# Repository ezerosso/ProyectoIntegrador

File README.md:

# Documentación para la implementación de un monitor de material particulado móvil

_Proyecto coparticipativo con la Secretaría de Ambiente de la provincia de Córdoba y la Facultad de Ciencias Exactas, físicas y Naturales de la Universidad Nacional de Córdoba._

(Después pondremos una foto con el plot bien termiando.)

## Guía práctica para la implementación del proyecto

A continuación se explicará la estructura del presente repositorio y los pasos a seguir. 

### En la carpeta Hardware se encuentra:
* Los componentes electrónicos necesarias para el dispositivo y dónde conseguirlos
* Implementación del circuito impreso PCB
* Implementación del Gabinete

### Instalación de software necesario:

* [Visual Studio Code](https://code.visualstudio.com/download) - Editor de código fuente donde se podrá visualizar el proyecto en su totalidad.

* [Extensión PlatformIo](https://platformio.org/install/ide?install=vscode) - Entorno de desarrollo Integrado (IDE) desde donde se podrá cargar el programa a la placa de desarollo.

* [Git Bash](https://gitforwindows.org/) - Software de control de versiones, necesario para [clonar el repositorio de GitHub](https://docs.github.com/es/repositories/creating-and-managing-repositories/cloning-a-repository) en nuestra PC. 

Una vez hecho esto, desde el VSC, se debe abrir el proyecto _(Archivo -> Abrir carpeta -> Buscamos en la carpeta donde se clonó el repositorio)._

A continuación se debe conectar mediante un cable USB la placa NodeMCU a cualquier puerto USB de nuestra PC. Luego cargamos el código a la placa:

Por último insertamos la Placa en los conectores de nuestra PCB como se indica en la carpeta Hardware.

Si se desea realizar una prueba preliminar, previo al montaje final, se puede realizar conexionando el circuito en una [protoboard](http://www.circuitoselectronicos.org/2007/10/el-protoboard-tableta-de-experimentacin.html) siguiendo el esquemático mostrado el el archivo esquematico.pdf que se encuentra en la carpeta KiCad (_Hardware -> Circuito impreso -> KiCad_).

<!-- *_Referencias_*

- https://programarfacil.com/blog/arduino-blog/platformio/

 -->

 # Manual de uso

 ## Acceso externo: Carga, Encendido y Extracción de microSD

Una vez se tenga el equipo implementado, en su parte inferior se tendrá acceso al switch on-off, a la extracción de la memoria microSD y al pin de carga:

 Los datos son guardados en archivos .csv que pueden ser visualizados en planillas de cálculo como el programa libre office, acomodados por día y agrupados en la carpeta Monitor PM.

(mostrar como se guardan los datos, como extraerlos y qué hacer con ellos)
(CONSULTAR A LA VIVI QUE HACER CON LOS DATOS)

 ## Pantallas y significados

 ### Una vez encendido el dispositivo cuenta con la siguiente pantalla de inicialización

#### #Si todo está correcto, es decir, todos los módulos funcionando y la tarjeta microSD insertada se espera que se encuentren los satélites necesarios mediante la interfaz gráfica animada mostrada a continación, dicha interfaz también se mostrará si se perdiera la señal en algún momento del recorrido. 

#### Si el tiempo de la interfaz de la búsqueda de satélites sumada a la de inicialización es menor a 30 segundos (tiempo necesario para la estabilización del sensor PM), se informa por pantalla de la siguiente forma:

#### Una vez estabilizado el sensor, con los satélites encontrados, la tarjeta microSD insertada y todo andando correctamente se imprime la pantalla general mostrada a continuación donde se refrescan los datos de los sensores en tiempo real que están siendo almacenados, y por otro lado también se informa el nivel de batería disponible.

#### Si desde el encendido o durante el normal funcionamiento del dispositivo se encuentra alguna falla, se informará mediante las pantallas mostradas a continuación:

##### - Se informa cuando la tarjeta microSD está mal insertada o no se encuentra los datos:

##### - Se informa cuando no se reciben datos del sensor PM, se dejan de registrar los datos:

##### - Se informa cuando no se recién datos del módulo GPS, se dejan de registrar los datos:

##### - Se informa cuando la batería está baja, no se muestran los datos pero se siguen registrando:

_Esta información también será valiosa durante el proceso de armado y pruebas del equipo, ya que informa sobre la mal conexión o funcionamiento de algún módulo o sensor._

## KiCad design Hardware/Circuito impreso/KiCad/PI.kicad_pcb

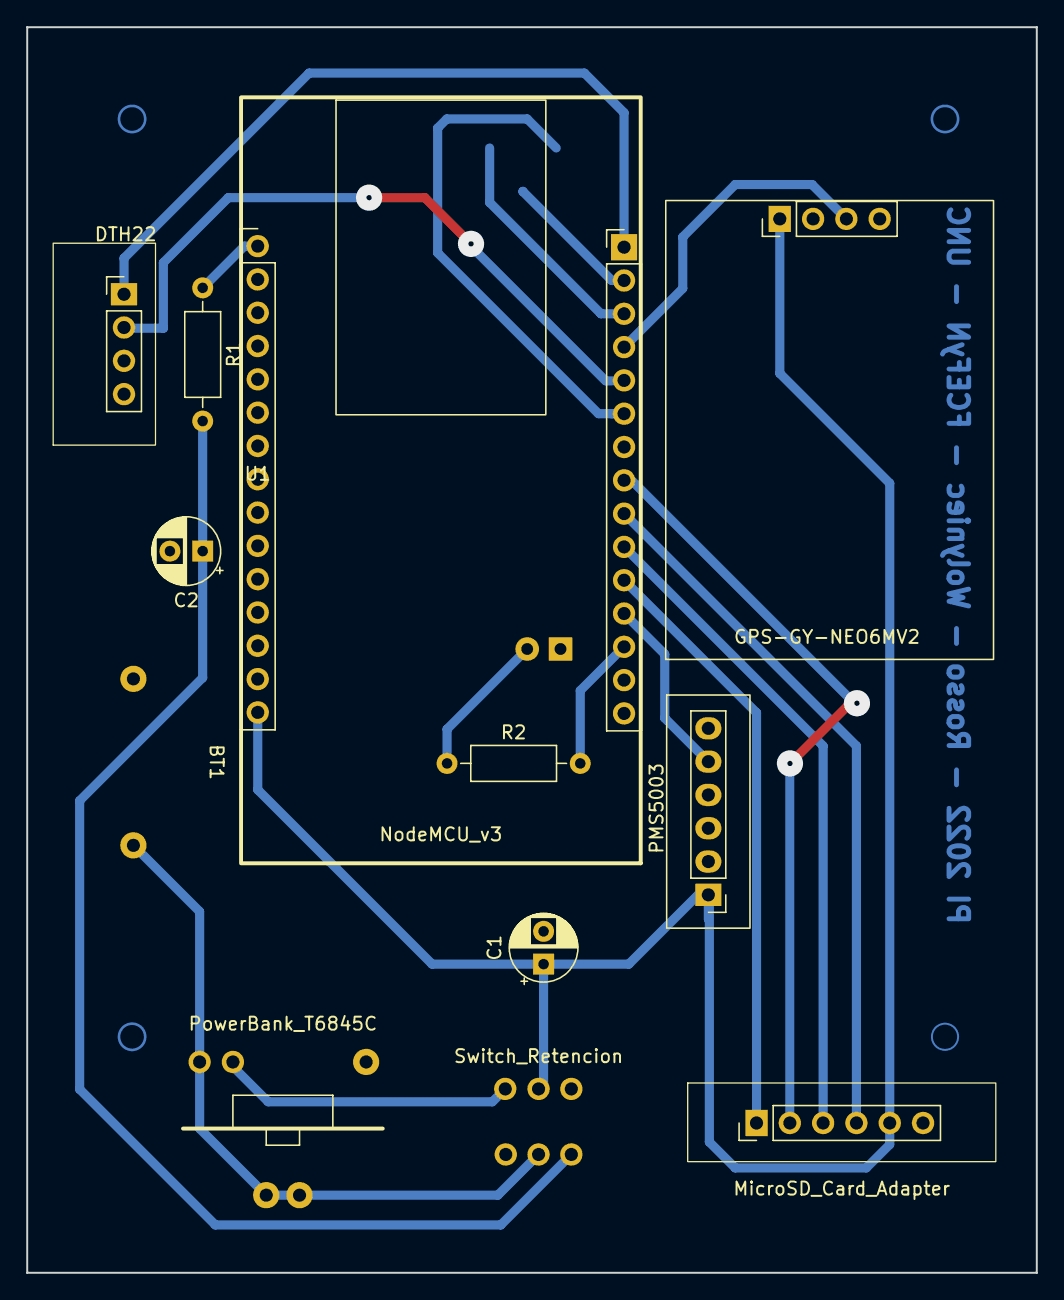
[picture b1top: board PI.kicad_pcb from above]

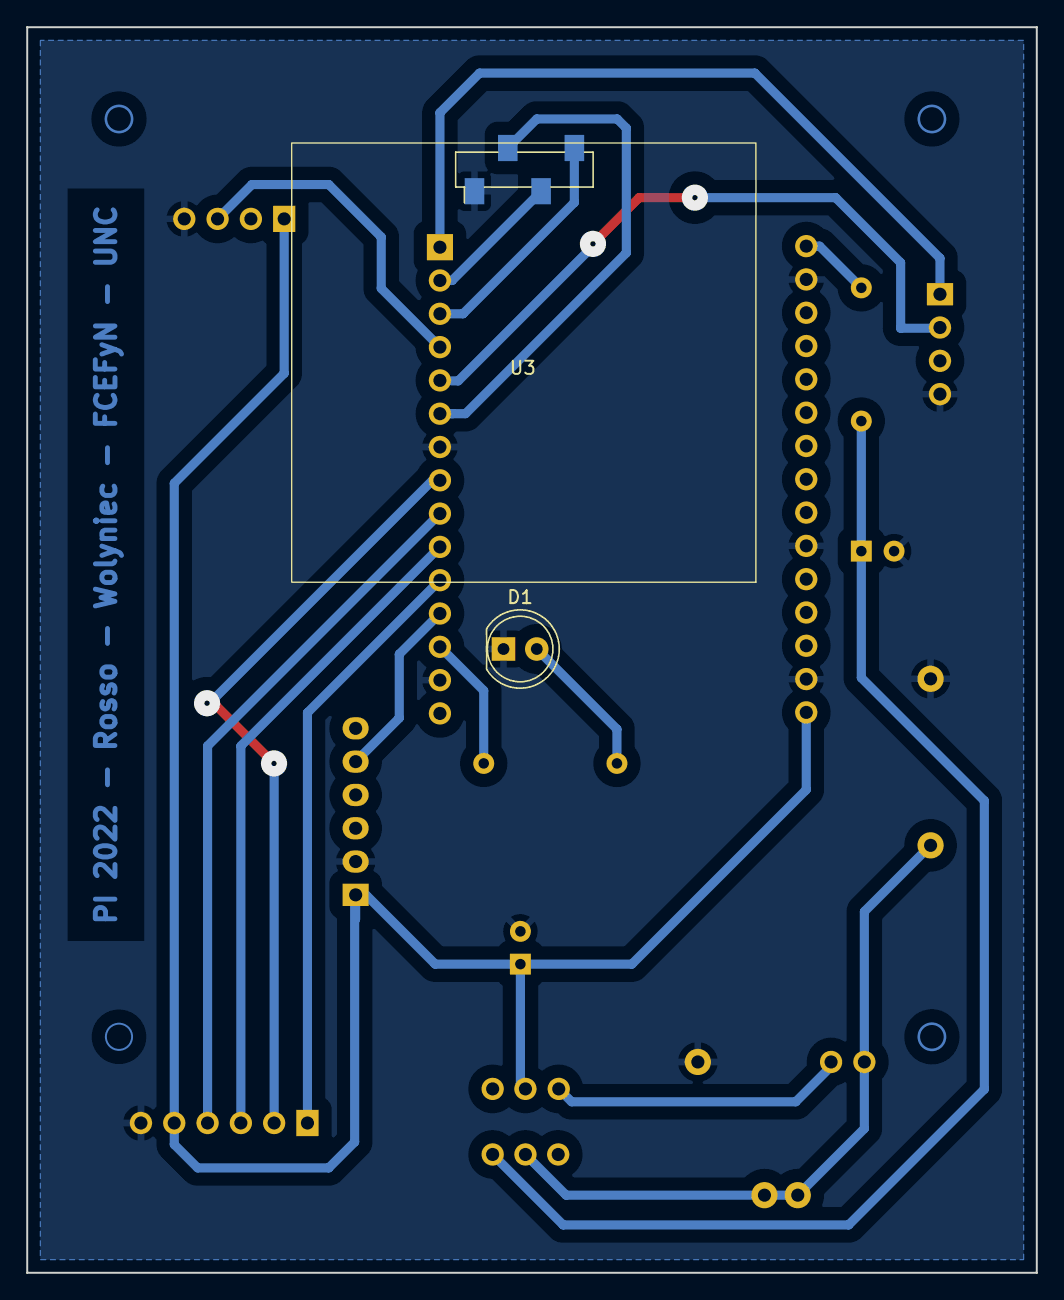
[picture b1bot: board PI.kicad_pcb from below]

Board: 2 copper layers, 77.0 x 95.0 mm, 14 parts (2 on the bottom side), 19 nets.

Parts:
BT1: Battery_Cell_3v7; battery_18650
C1, C2: C; CP_Radial_D5.0mm_P2.50mm
D1: LED; LED_D5.0mm
DTH22: DHT22
GPS-GY-NEO6MV2: GPS-GY-NEO6MV2
MicroSD_Card_Adapter: MicroSD_Card_Adapter; MicroSD_Card_adapter
PMS5003: PMS5003
PowerBank_T6845C: PowerBank_T6845C; StepUP_3.7_5v
R1: 100k; R_Axial_DIN0207_L6.3mm_D2.5mm_P10.16mm_Horizontal
R2: 220; R_Axial_DIN0207_L6.3mm_D2.5mm_P10.16mm_Horizontal
Switch_Retencion: Switch_Retencion
U1: NodeMCU_v3; NodeMCU_V3
U3: OLED-SH1106; OLED_SH1106_1.3''

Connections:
CS: MicroSD_Card_Adapter.1 (CS), U1.26 (D8)
DATA_DHT: DTH22.2 (DATA), U1.20 (D4)
GND: BT1.2 (-), C1.2, C2.2, D1.1 (K), DTH22.4 (GND), GPS-GY-NEO6MV2.4 (GND), MicroSD_Card_Adapter.6 (GND), PMS5003.2 (GND), PowerBank_T6845C.3 (GND), U1.2 (GND), U1.10 (GND), U1.14 (GND), U1.22 (GND), U1.29 (GND), U3.1 (GND)
MISO: MicroSD_Card_Adapter.4 (MISO), U1.24 (D6)
MOSI: MicroSD_Card_Adapter.3 (MOSI), U1.25 (D7)
unnamed: D1.2 (A), R2.1
unnamed: R1.1, U1.1 (A0)
unnamed: R2.2, U1.28 (TX)
SCK: MicroSD_Card_Adapter.2 (SCK), U1.23 (D5)
SCL: U1.17 (D1), U3.3 (SCL)
SDA: U1.18 (D2), U3.4 (SDA)
TX_GPS: GPS-GY-NEO6MV2.3 (TX), U1.19 (D3)
TX_PMS: PMS5003.5 (TX), U1.27 (RX)
VCC_3V3: GPS-GY-NEO6MV2.1 (VCC), U1.11 (3V3), U1.21 (3V3), U1.30 (3V3), U3.2 (VCC)
VCC_5V_IN: C1.1, MicroSD_Card_Adapter.5 (VCC), PMS5003.1 (VCC), Switch_Retencion.5, U1.15 (VIN)
VCC_5V_OUT: PowerBank_T6845C.2 (VCC_OUT), Switch_Retencion.4
VCC_IN_ADC: C2.1, R1.2, Switch_Retencion.3
VCC_OUT_BAT: BT1.1 (+), PowerBank_T6845C.1 (VCC_IN), Switch_Retencion.2
VCC_dht22: DTH22.1 (VCC), U1.16 (D0)

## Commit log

2022-04-27 primer commit
2022-04-27 se_agrega_carpeta_hardware_y_readme
2022-04-27 prueba
2022-04-27 pruebaTextoReadmeGeneral
2022-04-27 faso
2022-04-27 pruebaImagen
2022-04-27 carpetaImagenes
2022-04-27 imagenPrincipal
2022-04-27 faso2
2022-04-27 etiquetaDelCambio
2022-04-28 readmeGabinete
2022-04-28 readmecomponentes
2022-04-28 readmeGeneral
2022-04-29 adaptacionDeComponentes
2022-04-29 manual
